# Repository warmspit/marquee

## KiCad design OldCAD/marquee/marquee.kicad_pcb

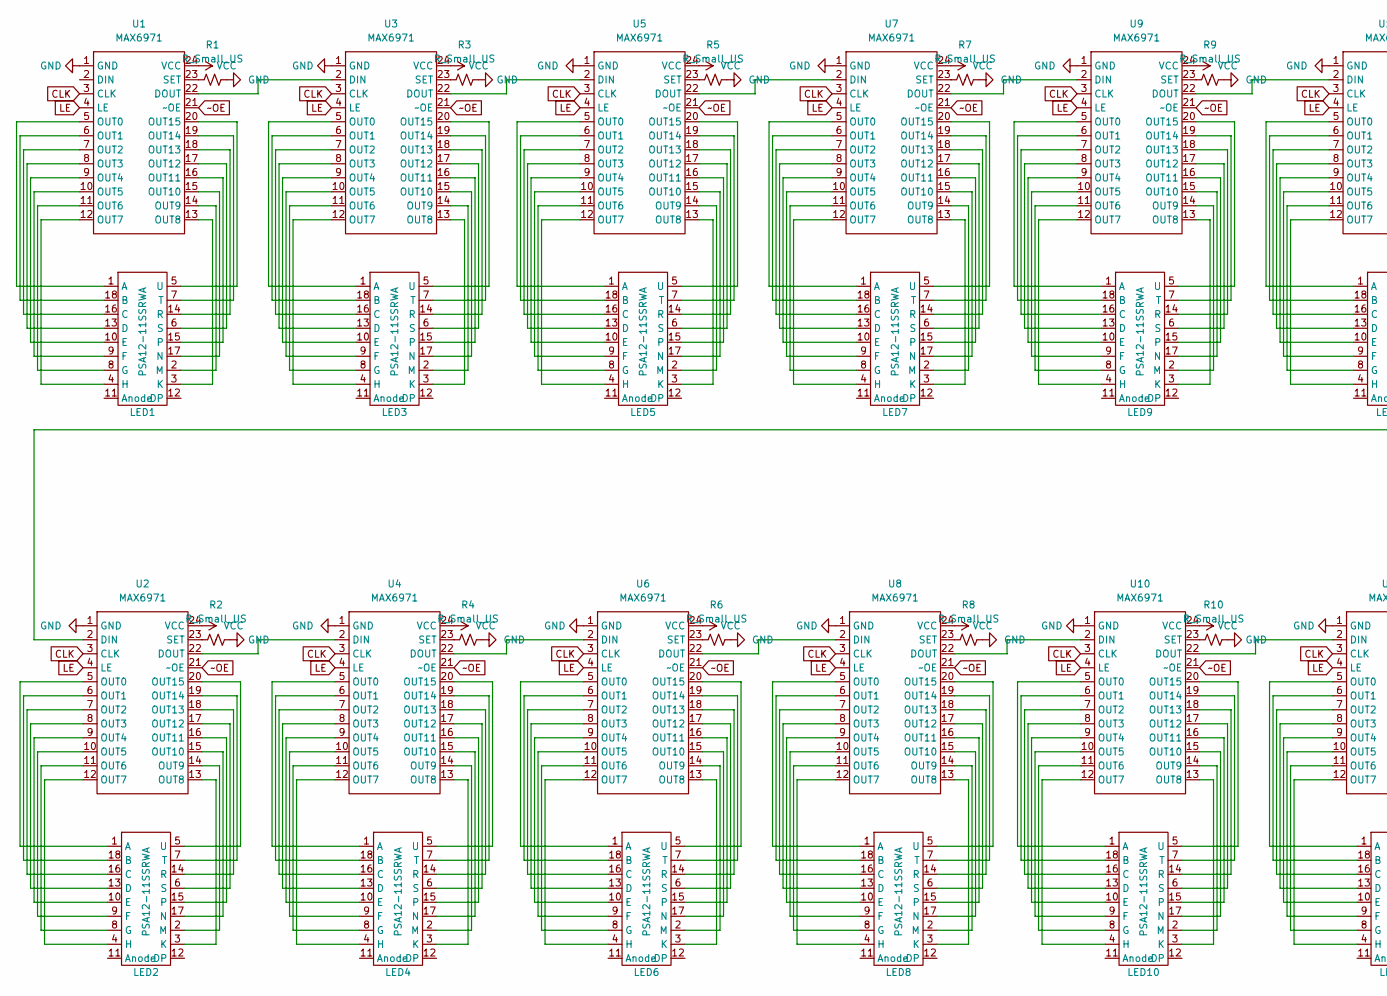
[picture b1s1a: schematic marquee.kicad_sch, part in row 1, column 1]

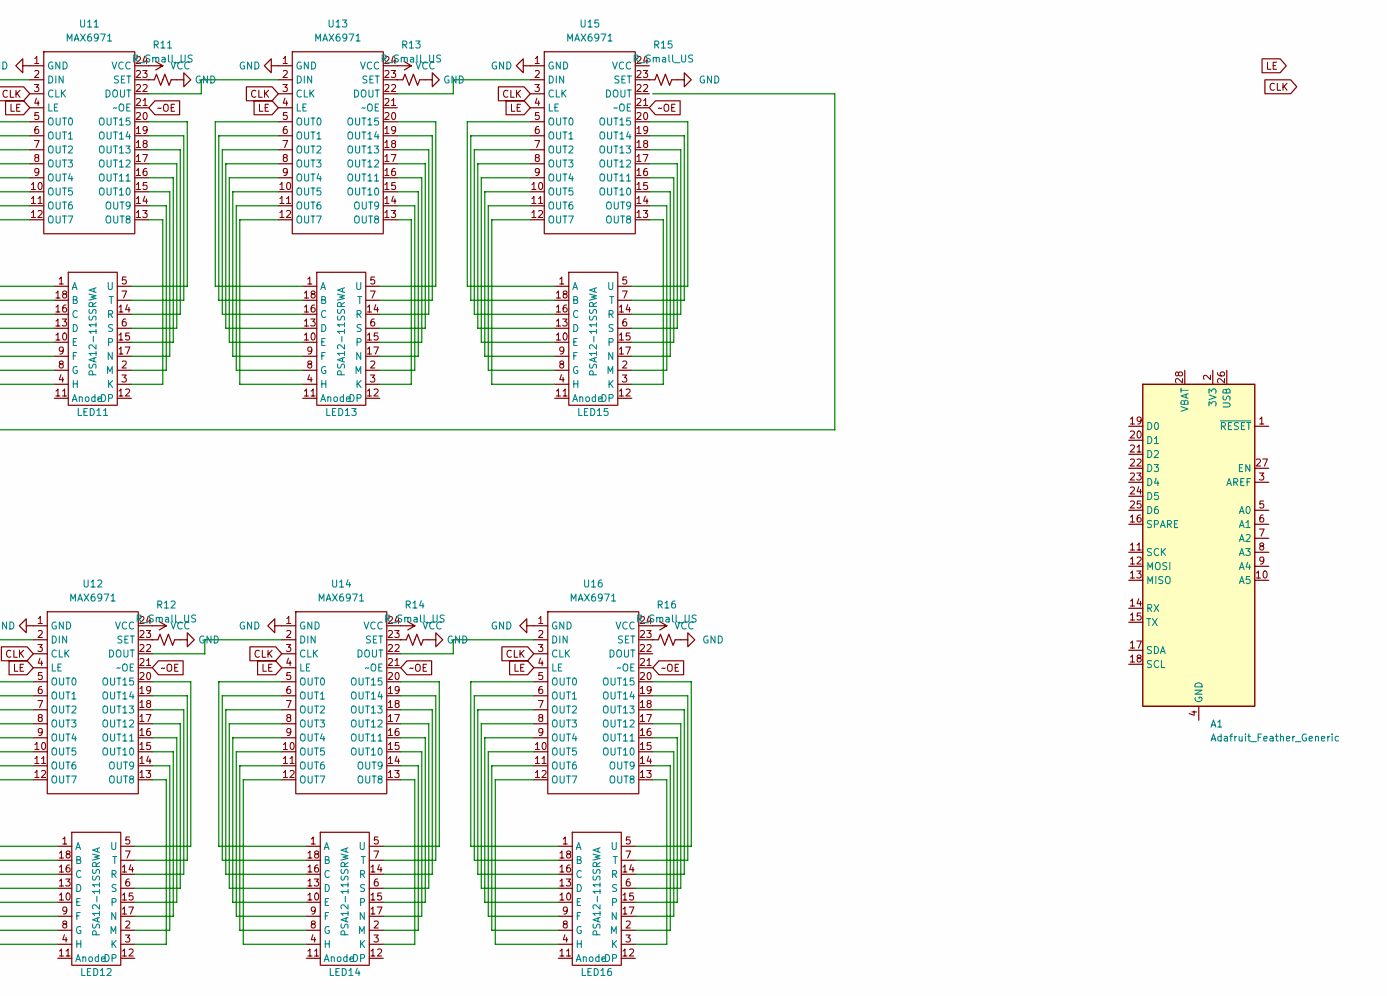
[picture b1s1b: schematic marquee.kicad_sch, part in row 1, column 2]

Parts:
A1: Adafruit_Feather_Generic; Adafruit_Feather
LED1, LED2, LED3, LED4, LED5, LED6, LED7, LED8, LED9, LED10, LED11, LED12, LED13, LED14, LED15, LED16: PSA12-11SSRWA; PSA12-11SRWA
R1, R2, R3, R4, R5, R6, R7, R8, R9, R10, R11, R12, R13, R14, R15, R16: R_Small_US; R_LDR_5.2x5.2mm_P3.5mm_Horizontal
U1, U2, U3, U4, U5, U6, U7, U8, U9, U10, U11, U12, U13, U14, U15, U16: MAX6971; DIP-24_W7.62mm_Socket

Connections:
CLK: U1.3 (CLK), U2.3 (CLK), U3.3 (CLK), U4.3 (CLK), U5.3 (CLK), U6.3 (CLK), U7.3 (CLK), U8.3 (CLK), U9.3 (CLK), U10.3 (CLK), U11.3 (CLK), U12.3 (CLK), U13.3 (CLK), U14.3 (CLK), U15.3 (CLK), U16.3 (CLK)
GND: R1.2, R2.2, R3.2, R4.2, R5.2, R6.2, R7.2, R8.2, R9.2, R10.2, R11.2, R12.2, R13.2, R14.2, R15.2, R16.2, U1.1 (GND), U2.1 (GND), U3.1 (GND), U4.1 (GND), U5.1 (GND), U6.1 (GND), U7.1 (GND), U8.1 (GND), U9.1 (GND), U10.1 (GND), U11.1 (GND), U12.1 (GND), U13.1 (GND), U14.1 (GND), U15.1 (GND), U16.1 (GND)
LE: U1.4 (LE), U2.4 (LE), U3.4 (LE), U4.4 (LE), U5.4 (LE), U6.4 (LE), U7.4 (LE), U8.4 (LE), U9.4 (LE), U10.4 (LE), U11.4 (LE), U12.4 (LE), U13.4 (LE), U14.4 (LE), U15.4 (LE), U16.4 (LE)
unnamed: LED1.1 (A), U1.5 (OUT0)
unnamed: LED1.2 (M), U1.14 (OUT9)
unnamed: LED1.3 (K), U1.13 (OUT8)
unnamed: LED1.4 (H), U1.12 (OUT7)
unnamed: LED1.5 (U), U1.20 (OUT15)
unnamed: LED1.6 (S), U1.17 (OUT12)
unnamed: LED1.7 (T), U1.19 (OUT14)
unnamed: LED1.8 (G), U1.11 (OUT6)
unnamed: LED1.9 (F), U1.10 (OUT5)
unnamed: LED1.10 (E), U1.9 (OUT4)
unnamed: LED1.13 (D), U1.8 (OUT3)
unnamed: LED1.14 (R), U1.18 (OUT13)
unnamed: LED1.15, U1.16 (OUT11)
unnamed: LED1.16 (C), U1.7 (OUT2)
unnamed: LED1.17 (N), U1.15 (OUT10)
unnamed: LED1.18 (B), U1.6 (OUT1)
unnamed: LED2.1 (A), U2.5 (OUT0)
unnamed: LED2.2 (M), U2.14 (OUT9)
unnamed: LED2.3 (K), U2.13 (OUT8)
unnamed: LED2.4 (H), U2.12 (OUT7)
unnamed: LED2.5 (U), U2.20 (OUT15)
unnamed: LED2.6 (S), U2.17 (OUT12)
unnamed: LED2.7 (T), U2.19 (OUT14)
unnamed: LED2.8 (G), U2.11 (OUT6)
unnamed: LED2.9 (F), U2.10 (OUT5)
unnamed: LED2.10 (E), U2.9 (OUT4)
unnamed: LED2.13 (D), U2.8 (OUT3)
unnamed: LED2.14 (R), U2.18 (OUT13)
unnamed: LED2.15, U2.16 (OUT11)
unnamed: LED2.16 (C), U2.7 (OUT2)
unnamed: LED2.17 (N), U2.15 (OUT10)
unnamed: LED2.18 (B), U2.6 (OUT1)
unnamed: LED3.1 (A), U3.5 (OUT0)
unnamed: LED3.2 (M), U3.14 (OUT9)
unnamed: LED3.3 (K), U3.13 (OUT8)
unnamed: LED3.4 (H), U3.12 (OUT7)
unnamed: LED3.5 (U), U3.20 (OUT15)
unnamed: LED3.6 (S), U3.17 (OUT12)
unnamed: LED3.7 (T), U3.19 (OUT14)
unnamed: LED3.8 (G), U3.11 (OUT6)
unnamed: LED3.9 (F), U3.10 (OUT5)
unnamed: LED3.10 (E), U3.9 (OUT4)
unnamed: LED3.13 (D), U3.8 (OUT3)
unnamed: LED3.14 (R), U3.18 (OUT13)
unnamed: LED3.15, U3.16 (OUT11)
unnamed: LED3.16 (C), U3.7 (OUT2)
unnamed: LED3.17 (N), U3.15 (OUT10)
unnamed: LED3.18 (B), U3.6 (OUT1)
unnamed: LED4.1 (A), U4.5 (OUT0)
unnamed: LED4.2 (M), U4.14 (OUT9)
unnamed: LED4.3 (K), U4.13 (OUT8)
unnamed: LED4.4 (H), U4.12 (OUT7)
unnamed: LED4.5 (U), U4.20 (OUT15)
unnamed: LED4.6 (S), U4.17 (OUT12)
unnamed: LED4.7 (T), U4.19 (OUT14)
unnamed: LED4.8 (G), U4.11 (OUT6)
unnamed: LED4.9 (F), U4.10 (OUT5)
unnamed: LED4.10 (E), U4.9 (OUT4)
unnamed: LED4.13 (D), U4.8 (OUT3)
unnamed: LED4.14 (R), U4.18 (OUT13)
unnamed: LED4.15, U4.16 (OUT11)
unnamed: LED4.16 (C), U4.7 (OUT2)
unnamed: LED4.17 (N), U4.15 (OUT10)
unnamed: LED4.18 (B), U4.6 (OUT1)
unnamed: LED5.1 (A), U5.5 (OUT0)
unnamed: LED5.2 (M), U5.14 (OUT9)
unnamed: LED5.3 (K), U5.13 (OUT8)
unnamed: LED5.4 (H), U5.12 (OUT7)
unnamed: LED5.5 (U), U5.20 (OUT15)
unnamed: LED5.6 (S), U5.17 (OUT12)
unnamed: LED5.7 (T), U5.19 (OUT14)
unnamed: LED5.8 (G), U5.11 (OUT6)
unnamed: LED5.9 (F), U5.10 (OUT5)
unnamed: LED5.10 (E), U5.9 (OUT4)
unnamed: LED5.13 (D), U5.8 (OUT3)
unnamed: LED5.14 (R), U5.18 (OUT13)
unnamed: LED5.15, U5.16 (OUT11)
unnamed: LED5.16 (C), U5.7 (OUT2)
unnamed: LED5.17 (N), U5.15 (OUT10)
unnamed: LED5.18 (B), U5.6 (OUT1)
unnamed: LED6.1 (A), U6.5 (OUT0)
unnamed: LED6.2 (M), U6.14 (OUT9)
unnamed: LED6.3 (K), U6.13 (OUT8)
unnamed: LED6.4 (H), U6.12 (OUT7)
unnamed: LED6.5 (U), U6.20 (OUT15)
unnamed: LED6.6 (S), U6.17 (OUT12)
unnamed: LED6.7 (T), U6.19 (OUT14)
unnamed: LED6.8 (G), U6.11 (OUT6)
unnamed: LED6.9 (F), U6.10 (OUT5)
unnamed: LED6.10 (E), U6.9 (OUT4)
unnamed: LED6.13 (D), U6.8 (OUT3)
unnamed: LED6.14 (R), U6.18 (OUT13)
unnamed: LED6.15, U6.16 (OUT11)
unnamed: LED6.16 (C), U6.7 (OUT2)
unnamed: LED6.17 (N), U6.15 (OUT10)
unnamed: LED6.18 (B), U6.6 (OUT1)
unnamed: LED7.1 (A), U7.5 (OUT0)
unnamed: LED7.2 (M), U7.14 (OUT9)
unnamed: LED7.3 (K), U7.13 (OUT8)
unnamed: LED7.4 (H), U7.12 (OUT7)
unnamed: LED7.5 (U), U7.20 (OUT15)
unnamed: LED7.6 (S), U7.17 (OUT12)
unnamed: LED7.7 (T), U7.19 (OUT14)
unnamed: LED7.8 (G), U7.11 (OUT6)
unnamed: LED7.9 (F), U7.10 (OUT5)
unnamed: LED7.10 (E), U7.9 (OUT4)
unnamed: LED7.13 (D), U7.8 (OUT3)
unnamed: LED7.14 (R), U7.18 (OUT13)
unnamed: LED7.15, U7.16 (OUT11)
unnamed: LED7.16 (C), U7.7 (OUT2)
unnamed: LED7.17 (N), U7.15 (OUT10)
unnamed: LED7.18 (B), U7.6 (OUT1)
unnamed: LED8.1 (A), U8.5 (OUT0)
unnamed: LED8.2 (M), U8.14 (OUT9)
unnamed: LED8.3 (K), U8.13 (OUT8)
unnamed: LED8.4 (H), U8.12 (OUT7)
unnamed: LED8.5 (U), U8.20 (OUT15)
unnamed: LED8.6 (S), U8.17 (OUT12)
unnamed: LED8.7 (T), U8.19 (OUT14)
unnamed: LED8.8 (G), U8.11 (OUT6)
unnamed: LED8.9 (F), U8.10 (OUT5)
unnamed: LED8.10 (E), U8.9 (OUT4)
unnamed: LED8.13 (D), U8.8 (OUT3)
unnamed: LED8.14 (R), U8.18 (OUT13)
unnamed: LED8.15, U8.16 (OUT11)
unnamed: LED8.16 (C), U8.7 (OUT2)
unnamed: LED8.17 (N), U8.15 (OUT10)
unnamed: LED8.18 (B), U8.6 (OUT1)
unnamed: LED9.1 (A), U9.5 (OUT0)
unnamed: LED9.2 (M), U9.14 (OUT9)
unnamed: LED9.3 (K), U9.13 (OUT8)
unnamed: LED9.4 (H), U9.12 (OUT7)
unnamed: LED9.5 (U), U9.20 (OUT15)
unnamed: LED9.6 (S), U9.17 (OUT12)
unnamed: LED9.7 (T), U9.19 (OUT14)
unnamed: LED9.8 (G), U9.11 (OUT6)
unnamed: LED9.9 (F), U9.10 (OUT5)
unnamed: LED9.10 (E), U9.9 (OUT4)
unnamed: LED9.13 (D), U9.8 (OUT3)
unnamed: LED9.14 (R), U9.18 (OUT13)
unnamed: LED9.15, U9.16 (OUT11)
unnamed: LED9.16 (C), U9.7 (OUT2)
unnamed: LED9.17 (N), U9.15 (OUT10)
unnamed: LED9.18 (B), U9.6 (OUT1)
unnamed: LED10.1 (A), U10.5 (OUT0)
unnamed: LED10.2 (M), U10.14 (OUT9)
unnamed: LED10.3 (K), U10.13 (OUT8)
unnamed: LED10.4 (H), U10.12 (OUT7)
unnamed: LED10.5 (U), U10.20 (OUT15)
unnamed: LED10.6 (S), U10.17 (OUT12)
unnamed: LED10.7 (T), U10.19 (OUT14)
unnamed: LED10.8 (G), U10.11 (OUT6)
unnamed: LED10.9 (F), U10.10 (OUT5)
unnamed: LED10.10 (E), U10.9 (OUT4)
unnamed: LED10.13 (D), U10.8 (OUT3)
unnamed: LED10.14 (R), U10.18 (OUT13)
unnamed: LED10.15, U10.16 (OUT11)
unnamed: LED10.16 (C), U10.7 (OUT2)
unnamed: LED10.17 (N), U10.15 (OUT10)
unnamed: LED10.18 (B), U10.6 (OUT1)
unnamed: LED11.1 (A), U11.5 (OUT0)
unnamed: LED11.2 (M), U11.14 (OUT9)
unnamed: LED11.3 (K), U11.13 (OUT8)
unnamed: LED11.4 (H), U11.12 (OUT7)
unnamed: LED11.5 (U), U11.20 (OUT15)
unnamed: LED11.6 (S), U11.17 (OUT12)
unnamed: LED11.7 (T), U11.19 (OUT14)
unnamed: LED11.8 (G), U11.11 (OUT6)
unnamed: LED11.9 (F), U11.10 (OUT5)
unnamed: LED11.10 (E), U11.9 (OUT4)
unnamed: LED11.13 (D), U11.8 (OUT3)
unnamed: LED11.14 (R), U11.18 (OUT13)
unnamed: LED11.15, U11.16 (OUT11)
unnamed: LED11.16 (C), U11.7 (OUT2)
unnamed: LED11.17 (N), U11.15 (OUT10)
unnamed: LED11.18 (B), U11.6 (OUT1)
unnamed: LED12.1 (A), U12.5 (OUT0)
unnamed: LED12.2 (M), U12.14 (OUT9)
unnamed: LED12.3 (K), U12.13 (OUT8)
unnamed: LED12.4 (H), U12.12 (OUT7)
unnamed: LED12.5 (U), U12.20 (OUT15)
unnamed: LED12.6 (S), U12.17 (OUT12)
unnamed: LED12.7 (T), U12.19 (OUT14)
unnamed: LED12.8 (G), U12.11 (OUT6)
unnamed: LED12.9 (F), U12.10 (OUT5)
unnamed: LED12.10 (E), U12.9 (OUT4)
unnamed: LED12.13 (D), U12.8 (OUT3)
unnamed: LED12.14 (R), U12.18 (OUT13)
unnamed: LED12.15, U12.16 (OUT11)
unnamed: LED12.16 (C), U12.7 (OUT2)
unnamed: LED12.17 (N), U12.15 (OUT10)
unnamed: LED12.18 (B), U12.6 (OUT1)
unnamed: LED13.1 (A), U13.5 (OUT0)
unnamed: LED13.2 (M), U13.14 (OUT9)
unnamed: LED13.3 (K), U13.13 (OUT8)
unnamed: LED13.4 (H), U13.12 (OUT7)
unnamed: LED13.5 (U), U13.20 (OUT15)
unnamed: LED13.6 (S), U13.17 (OUT12)
unnamed: LED13.7 (T), U13.19 (OUT14)
unnamed: LED13.8 (G), U13.11 (OUT6)
unnamed: LED13.9 (F), U13.10 (OUT5)
unnamed: LED13.10 (E), U13.9 (OUT4)
unnamed: LED13.13 (D), U13.8 (OUT3)
unnamed: LED13.14 (R), U13.18 (OUT13)
unnamed: LED13.15, U13.16 (OUT11)
unnamed: LED13.16 (C), U13.7 (OUT2)
unnamed: LED13.17 (N), U13.15 (OUT10)
unnamed: LED13.18 (B), U13.6 (OUT1)
unnamed: LED14.1 (A), U14.5 (OUT0)
unnamed: LED14.2 (M), U14.14 (OUT9)
unnamed: LED14.3 (K), U14.13 (OUT8)
unnamed: LED14.4 (H), U14.12 (OUT7)
unnamed: LED14.5 (U), U14.20 (OUT15)
unnamed: LED14.6 (S), U14.17 (OUT12)
unnamed: LED14.7 (T), U14.19 (OUT14)
unnamed: LED14.8 (G), U14.11 (OUT6)
unnamed: LED14.9 (F), U14.10 (OUT5)
unnamed: LED14.10 (E), U14.9 (OUT4)
unnamed: LED14.13 (D), U14.8 (OUT3)
unnamed: LED14.14 (R), U14.18 (OUT13)
unnamed: LED14.15, U14.16 (OUT11)
unnamed: LED14.16 (C), U14.7 (OUT2)
unnamed: LED14.17 (N), U14.15 (OUT10)
unnamed: LED14.18 (B), U14.6 (OUT1)
unnamed: LED15.1 (A), U15.5 (OUT0)
unnamed: LED15.2 (M), U15.14 (OUT9)
unnamed: LED15.3 (K), U15.13 (OUT8)
unnamed: LED15.4 (H), U15.12 (OUT7)
unnamed: LED15.5 (U), U15.20 (OUT15)
unnamed: LED15.6 (S), U15.17 (OUT12)
unnamed: LED15.7 (T), U15.19 (OUT14)
unnamed: LED15.8 (G), U15.11 (OUT6)
unnamed: LED15.9 (F), U15.10 (OUT5)
unnamed: LED15.10 (E), U15.9 (OUT4)
unnamed: LED15.13 (D), U15.8 (OUT3)
unnamed: LED15.14 (R), U15.18 (OUT13)
unnamed: LED15.15, U15.16 (OUT11)
unnamed: LED15.16 (C), U15.7 (OUT2)
unnamed: LED15.17 (N), U15.15 (OUT10)
unnamed: LED15.18 (B), U15.6 (OUT1)
unnamed: LED16.1 (A), U16.5 (OUT0)
unnamed: LED16.2 (M), U16.14 (OUT9)
unnamed: LED16.3 (K), U16.13 (OUT8)
unnamed: LED16.4 (H), U16.12 (OUT7)
unnamed: LED16.5 (U), U16.20 (OUT15)
unnamed: LED16.6 (S), U16.17 (OUT12)
unnamed: LED16.7 (T), U16.19 (OUT14)
unnamed: LED16.8 (G), U16.11 (OUT6)
unnamed: LED16.9 (F), U16.10 (OUT5)
unnamed: LED16.10 (E), U16.9 (OUT4)
unnamed: LED16.13 (D), U16.8 (OUT3)
unnamed: LED16.14 (R), U16.18 (OUT13)
unnamed: LED16.15, U16.16 (OUT11)
unnamed: LED16.16 (C), U16.7 (OUT2)
unnamed: LED16.17 (N), U16.15 (OUT10)
unnamed: LED16.18 (B), U16.6 (OUT1)
unnamed: R1.1, U1.23 (SET)
unnamed: R2.1, U2.23 (SET)
unnamed: R3.1, U3.23 (SET)
unnamed: R4.1, U4.23 (SET)
unnamed: R5.1, U5.23 (SET)
unnamed: R6.1, U6.23 (SET)
unnamed: R7.1, U7.23 (SET)
unnamed: R8.1, U8.23 (SET)
unnamed: R9.1, U9.23 (SET)
unnamed: R10.1, U10.23 (SET)
unnamed: R11.1, U11.23 (SET)
unnamed: R12.1, U12.23 (SET)
unnamed: R13.1, U13.23 (SET)
unnamed: R14.1, U14.23 (SET)
unnamed: R15.1, U15.23 (SET)
unnamed: R16.1, U16.23 (SET)
unnamed: U1.22 (DOUT), U3.2 (DIN)
unnamed: U2.22 (DOUT), U4.2 (DIN)
unnamed: U3.22 (DOUT), U5.2 (DIN)
unnamed: U4.22 (DOUT), U6.2 (DIN)
unnamed: U5.22 (DOUT), U7.2 (DIN)
unnamed: U6.22 (DOUT), U8.2 (DIN)
unnamed: U7.22 (DOUT), U9.2 (DIN)
unnamed: U8.22 (DOUT), U10.2 (DIN)
unnamed: U10.22 (DOUT), U12.2 (DIN)
unnamed: U9.22 (DOUT), U11.2 (DIN)
unnamed: U11.22 (DOUT), U13.2 (DIN)
unnamed: U12.22 (DOUT), U14.2 (DIN)
unnamed: U13.22 (DOUT), U15.2 (DIN)
unnamed: U14.22 (DOUT), U16.2 (DIN)
VCC: U1.24 (VCC), U2.24 (VCC), U3.24 (VCC), U4.24 (VCC), U5.24 (VCC), U6.24 (VCC), U7.24 (VCC), U8.24 (VCC), U9.24 (VCC), U10.24 (VCC), U11.24 (VCC), U12.24 (VCC), U13.24 (VCC), U14.24 (VCC), U16.24 (VCC)
~OE: U1.21 (~OE), U2.21 (~OE), U3.21 (~OE), U4.21 (~OE), U5.21 (~OE), U6.21 (~OE), U7.21 (~OE), U8.21 (~OE), U9.21 (~OE), U10.21 (~OE), U11.21 (~OE), U12.21 (~OE), U14.21 (~OE), U15.21 (~OE), U16.21 (~OE)

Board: 4 copper layers, 49 parts (32 on the bottom side), 291 nets, no tracks yet.

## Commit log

2023-01-15 add repo
2023-01-16 add gitignore
2023-01-16 add pcb, schematic
2023-01-25 move CAD to oldCAD change schematics from KiCAD to Diptrace
2023-02-01 remove old CAD
